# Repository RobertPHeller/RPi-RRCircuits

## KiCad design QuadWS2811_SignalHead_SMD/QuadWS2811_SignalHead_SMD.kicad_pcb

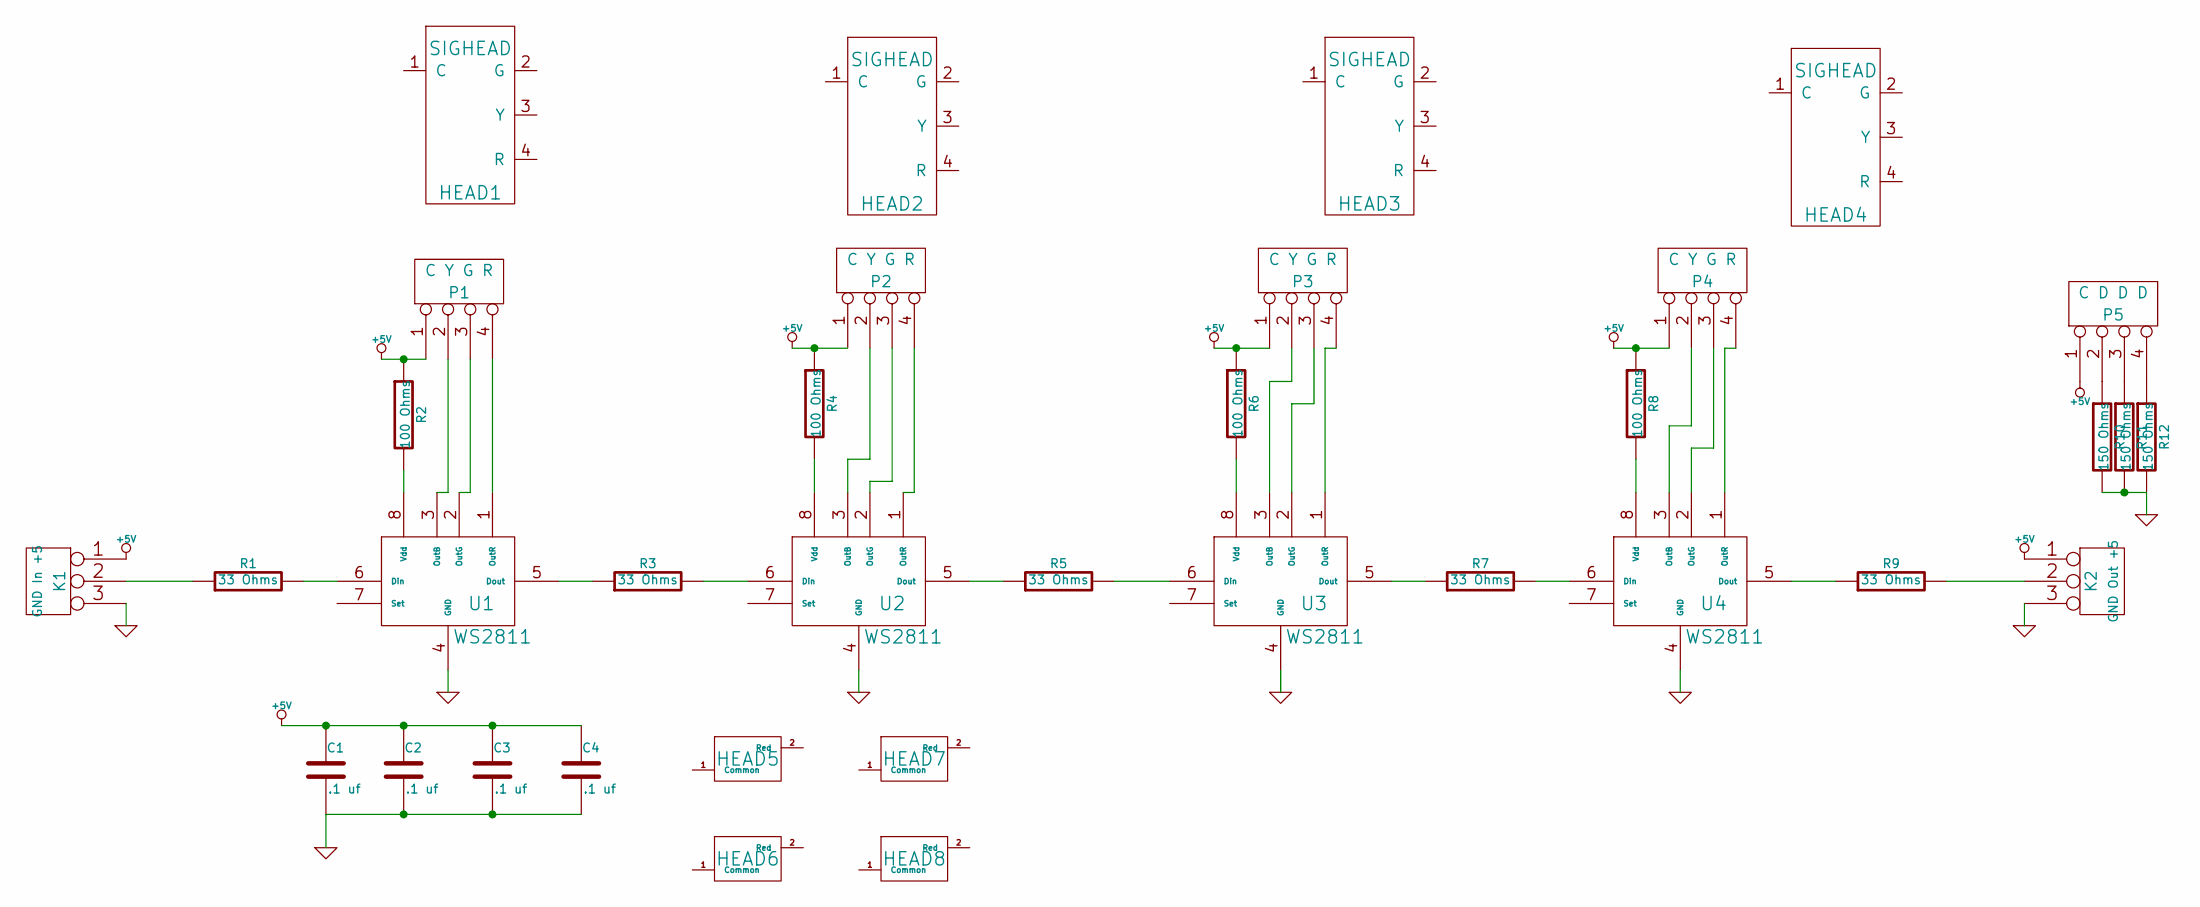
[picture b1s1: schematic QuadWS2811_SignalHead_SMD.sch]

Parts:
C1, C2, C3, C4: .1 uf
HEAD1, HEAD2, HEAD3, HEAD4: SIGHEAD
HEAD5, HEAD6, HEAD7, HEAD8: DUMMY
K1: GND In +5
K2: GND Out +5
P1, P2, P3, P4: C Y G R
P5: C D D D
R1, R3, R5, R7, R9: 33 Ohms
R2, R4, R6, R8: 100 Ohms
R10, R11, R12: 150 Ohms
U1, U2, U3, U4: WS2811

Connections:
+5V: C1.1, C2.1, C3.1, C4.1, K1.1, K2.1, P1.1, P2.1, P3.1, P4.1, P5.1, R2.1, R4.1, R6.1, R8.1
GND: C1.2, C2.2, C3.2, C4.2, K1.3, K2.3, R10.2, R11.2, R12.2, U1.4 (GND), U2.4 (GND), U3.4 (GND), U4.4 (GND)
unnamed: R2.2, U1.8 (Vdd)
unnamed: P1.2, U1.3 (OutB)
unnamed: P1.3, U1.2 (OutG)
unnamed: P1.4, U1.1 (OutR)
unnamed: R4.2, U2.8 (Vdd)
unnamed: P2.2, U2.3 (OutB)
unnamed: P4.4, U4.1 (OutR)
unnamed: P5.2, R10.1
unnamed: P5.3, R11.1
unnamed: P5.4, R12.1
unnamed: P2.3, U2.2 (OutG)
unnamed: P2.4, U2.1 (OutR)
unnamed: R6.2, U3.8 (Vdd)
unnamed: P3.2, U3.3 (OutB)
unnamed: P3.3, U3.2 (OutG)
unnamed: P3.4, U3.1 (OutR)
unnamed: P4.2, U4.3 (OutB)
unnamed: R8.2, U4.8 (Vdd)
unnamed: P4.3, U4.2 (OutG)
unnamed: R7.2, U4.6 (Din)
unnamed: R9.1, U4.5 (Dout)
unnamed: R3.1, U1.5 (Dout)
unnamed: R1.2, U1.6 (Din)
unnamed: R5.1, U2.5 (Dout)
unnamed: R3.2, U2.6 (Din)
unnamed: R7.1, U3.5 (Dout)
unnamed: R5.2, U3.6 (Din)
unnamed: K1.2 (PM), R1.1
unnamed: K2.2 (PM), R9.2

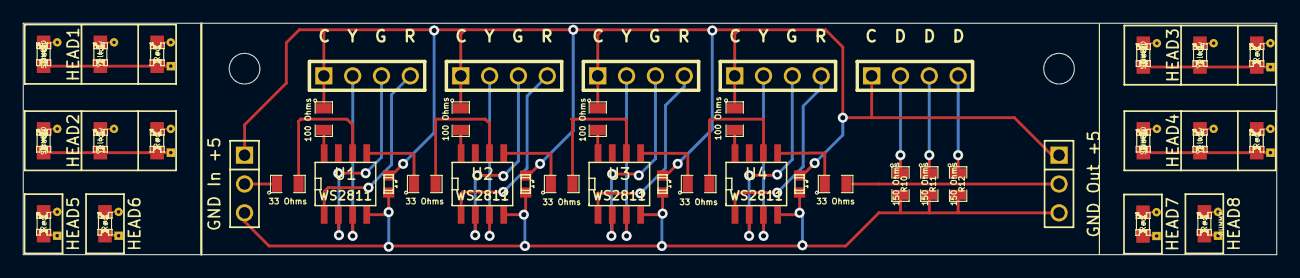
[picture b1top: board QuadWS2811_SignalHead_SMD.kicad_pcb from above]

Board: 2 copper layers, 110.4 x 20.4 mm, 37 parts (0 on the bottom side), 31 nets.

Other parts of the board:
MH: MountingHole_2-7mm_RevA_Date21Jun2010
MH#2: MountingHole_2-7mm_RevA_Date21Jun2010

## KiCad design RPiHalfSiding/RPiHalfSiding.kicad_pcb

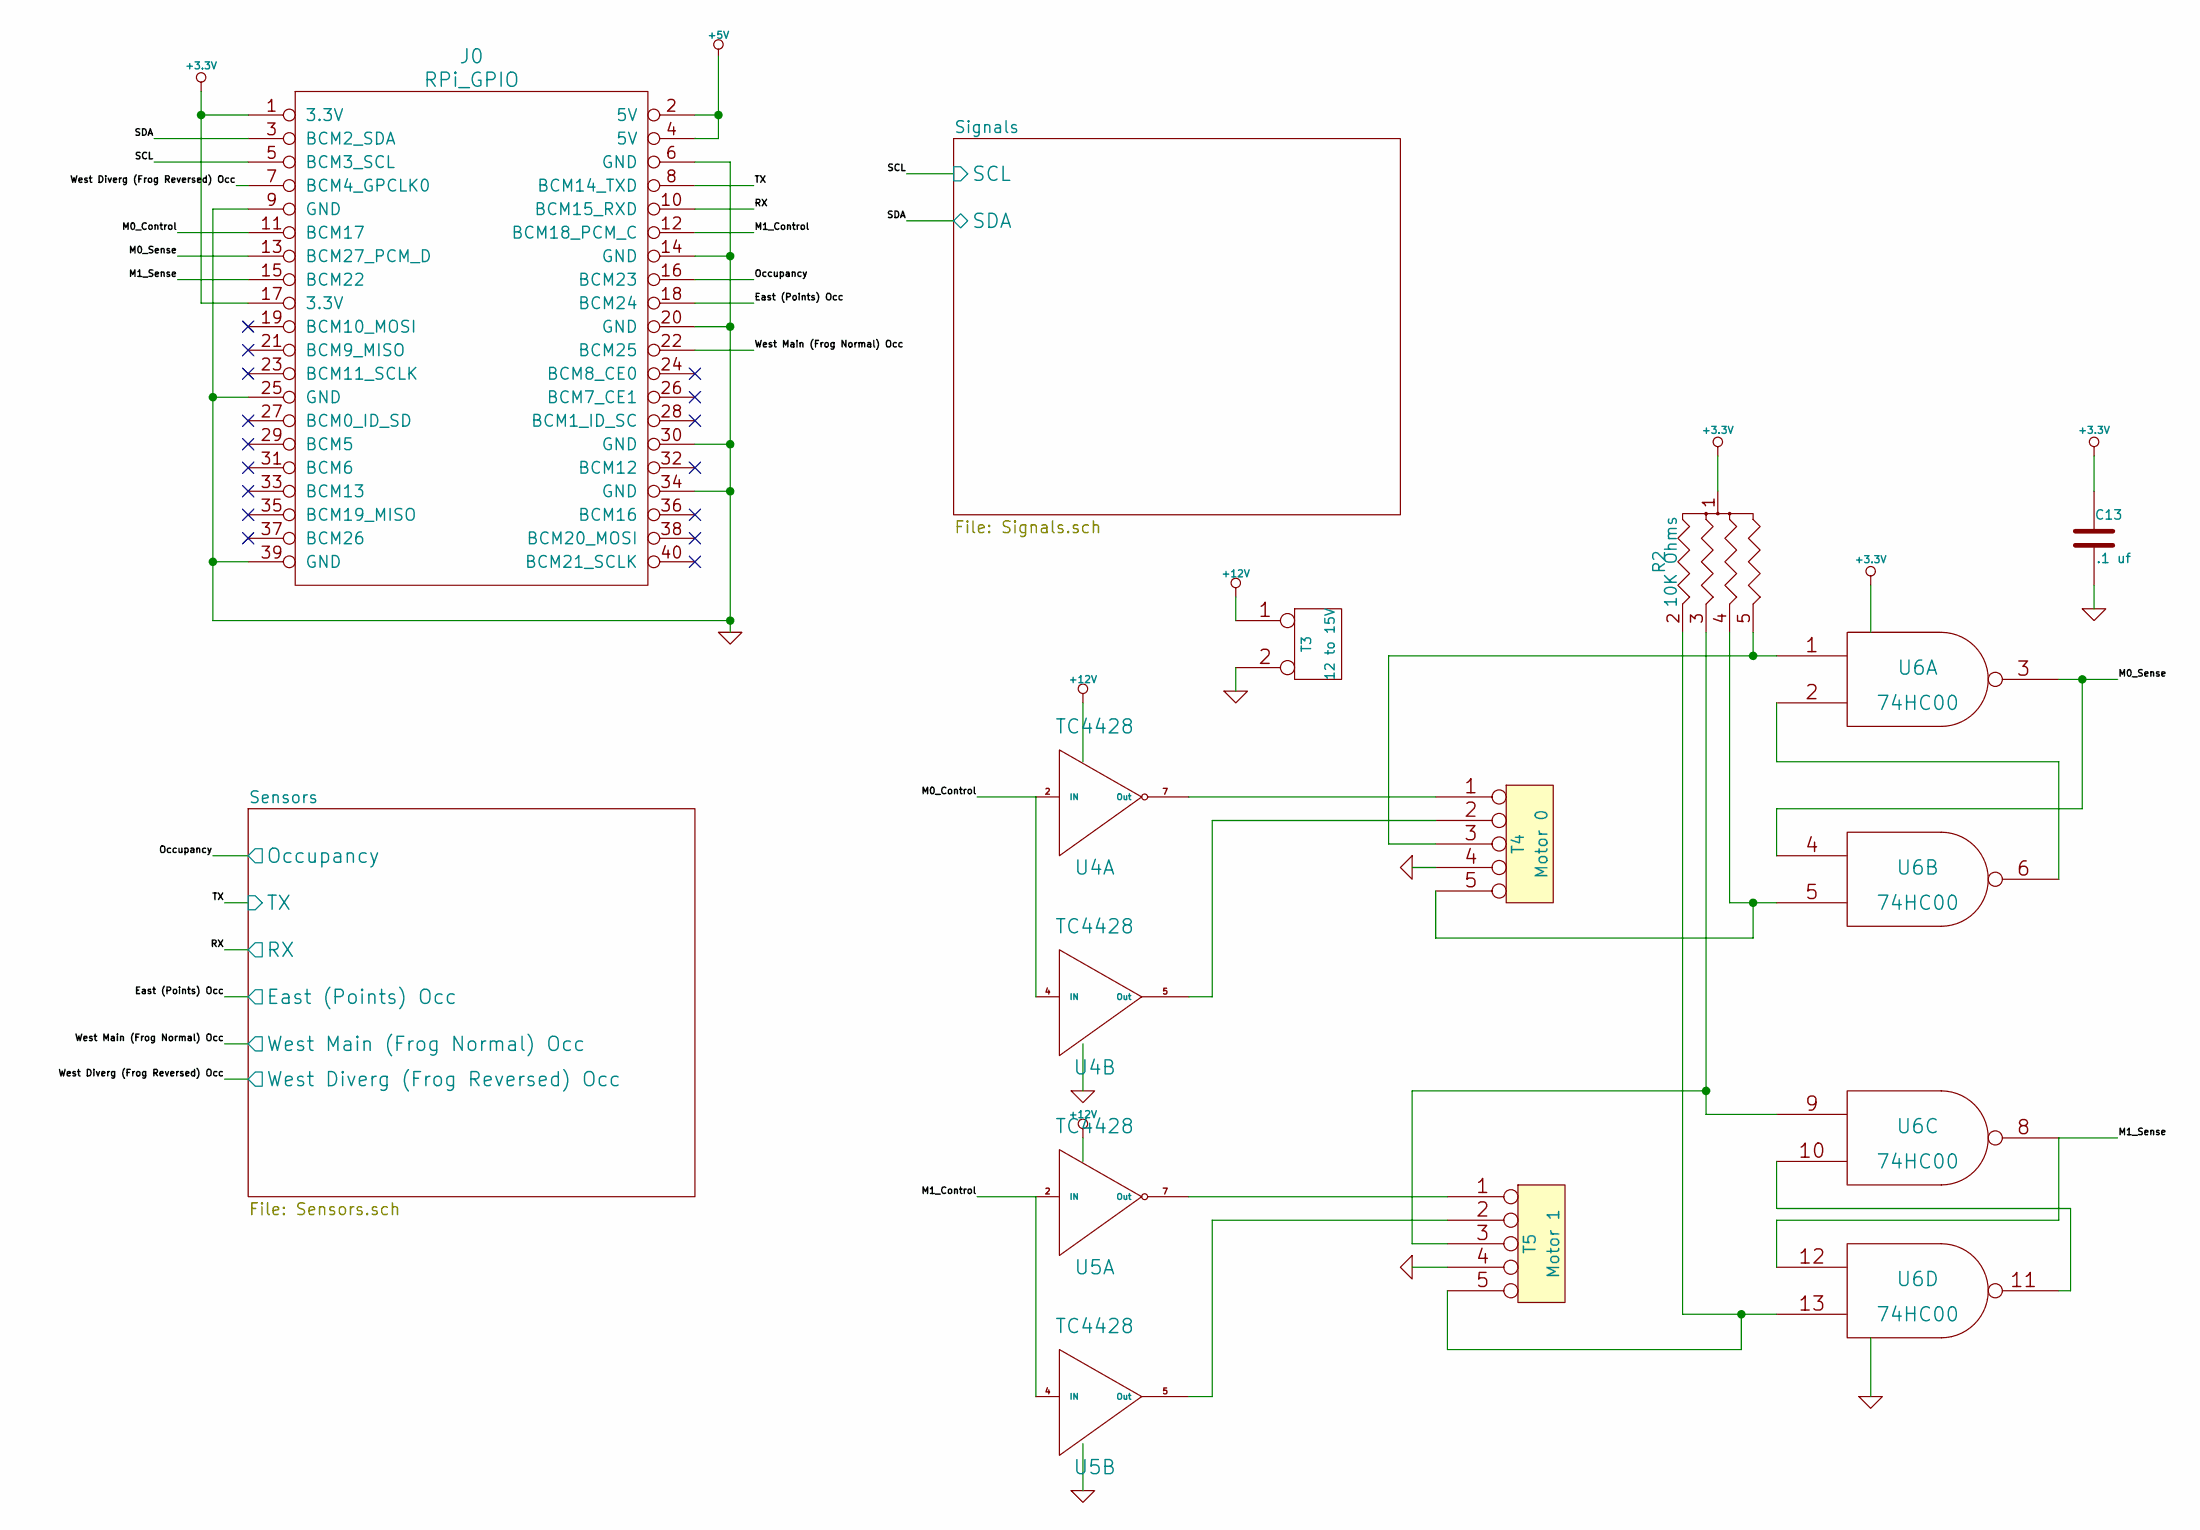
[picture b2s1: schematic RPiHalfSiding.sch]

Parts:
C13: .1 uf
J0: RPi_GPIO; Pin_Header_Straight_2x20
R2: 10K Ohms
T3: 12 to 15V
T4: Motor 0
T5: Motor 1
U4, U5: TC4428
U6: 74HC00

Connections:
+3.3V: C13.1, J0.1 (3.3V), J0.17 (3.3V), R2.1, U6.14 (VCC); also elsewhere on the board
+5V: J0.2 (5V), J0.4 (5V); also elsewhere on the board
+12V: T3.1, U4.6 (Vdd), U5.6 (Vdd)
/M0_Control: J0.11 (BCM17), U4.2 (IN), U4.4 (IN)
/M0_Sense: J0.13 (BCM27_PCM_D), U6.3, U6.4
/M1_Control: J0.12 (BCM18_PCM_C), U5.2 (IN), U5.4 (IN)
/M1_Sense: J0.15 (BCM22), U6.8, U6.12
/Sensors/East (Points) Occ: J0.18 (BCM24); also elsewhere on the board
/Sensors/Occupancy: J0.16 (BCM23); also elsewhere on the board
/Sensors/RX: J0.10 (BCM15_RXD); also elsewhere on the board
/Sensors/TX: J0.8 (BCM14_TXD); also elsewhere on the board
/Sensors/West Diverg (Frog Reversed) Occ: J0.7 (BCM4_GPCLK0); also elsewhere on the board
/Sensors/West Main (Frog Normal) Occ: J0.22 (BCM25); also elsewhere on the board
/Signals/SCL: J0.5 (BCM3_SCL); also elsewhere on the board
/Signals/SDA: J0.3 (BCM2_SDA); also elsewhere on the board
GND: C13.2, J0.6 (GND), J0.9 (GND), J0.14 (GND), J0.20 (GND), J0.25 (GND), J0.30 (GND), J0.34 (GND), J0.39 (GND), T3.2 (PM), T4.4, T5.4, U4.3 (GND), U5.3 (GND), U6.7 (GND); also elsewhere on the board
unnamed: U6.2, U6.6
unnamed: U6.10, U6.11
unnamed: T5.2, U5.5 (Out)
unnamed: R2.2, T5.5, U6.13
unnamed: R2.3, T5.3, U6.9
unnamed: R2.4, T4.5, U6.5
unnamed: R2.5, T4.3, U6.1
unnamed: T5.1, U5.7 (Out)
unnamed: T4.2, U4.5 (Out)
unnamed: T4.1, U4.7 (Out)

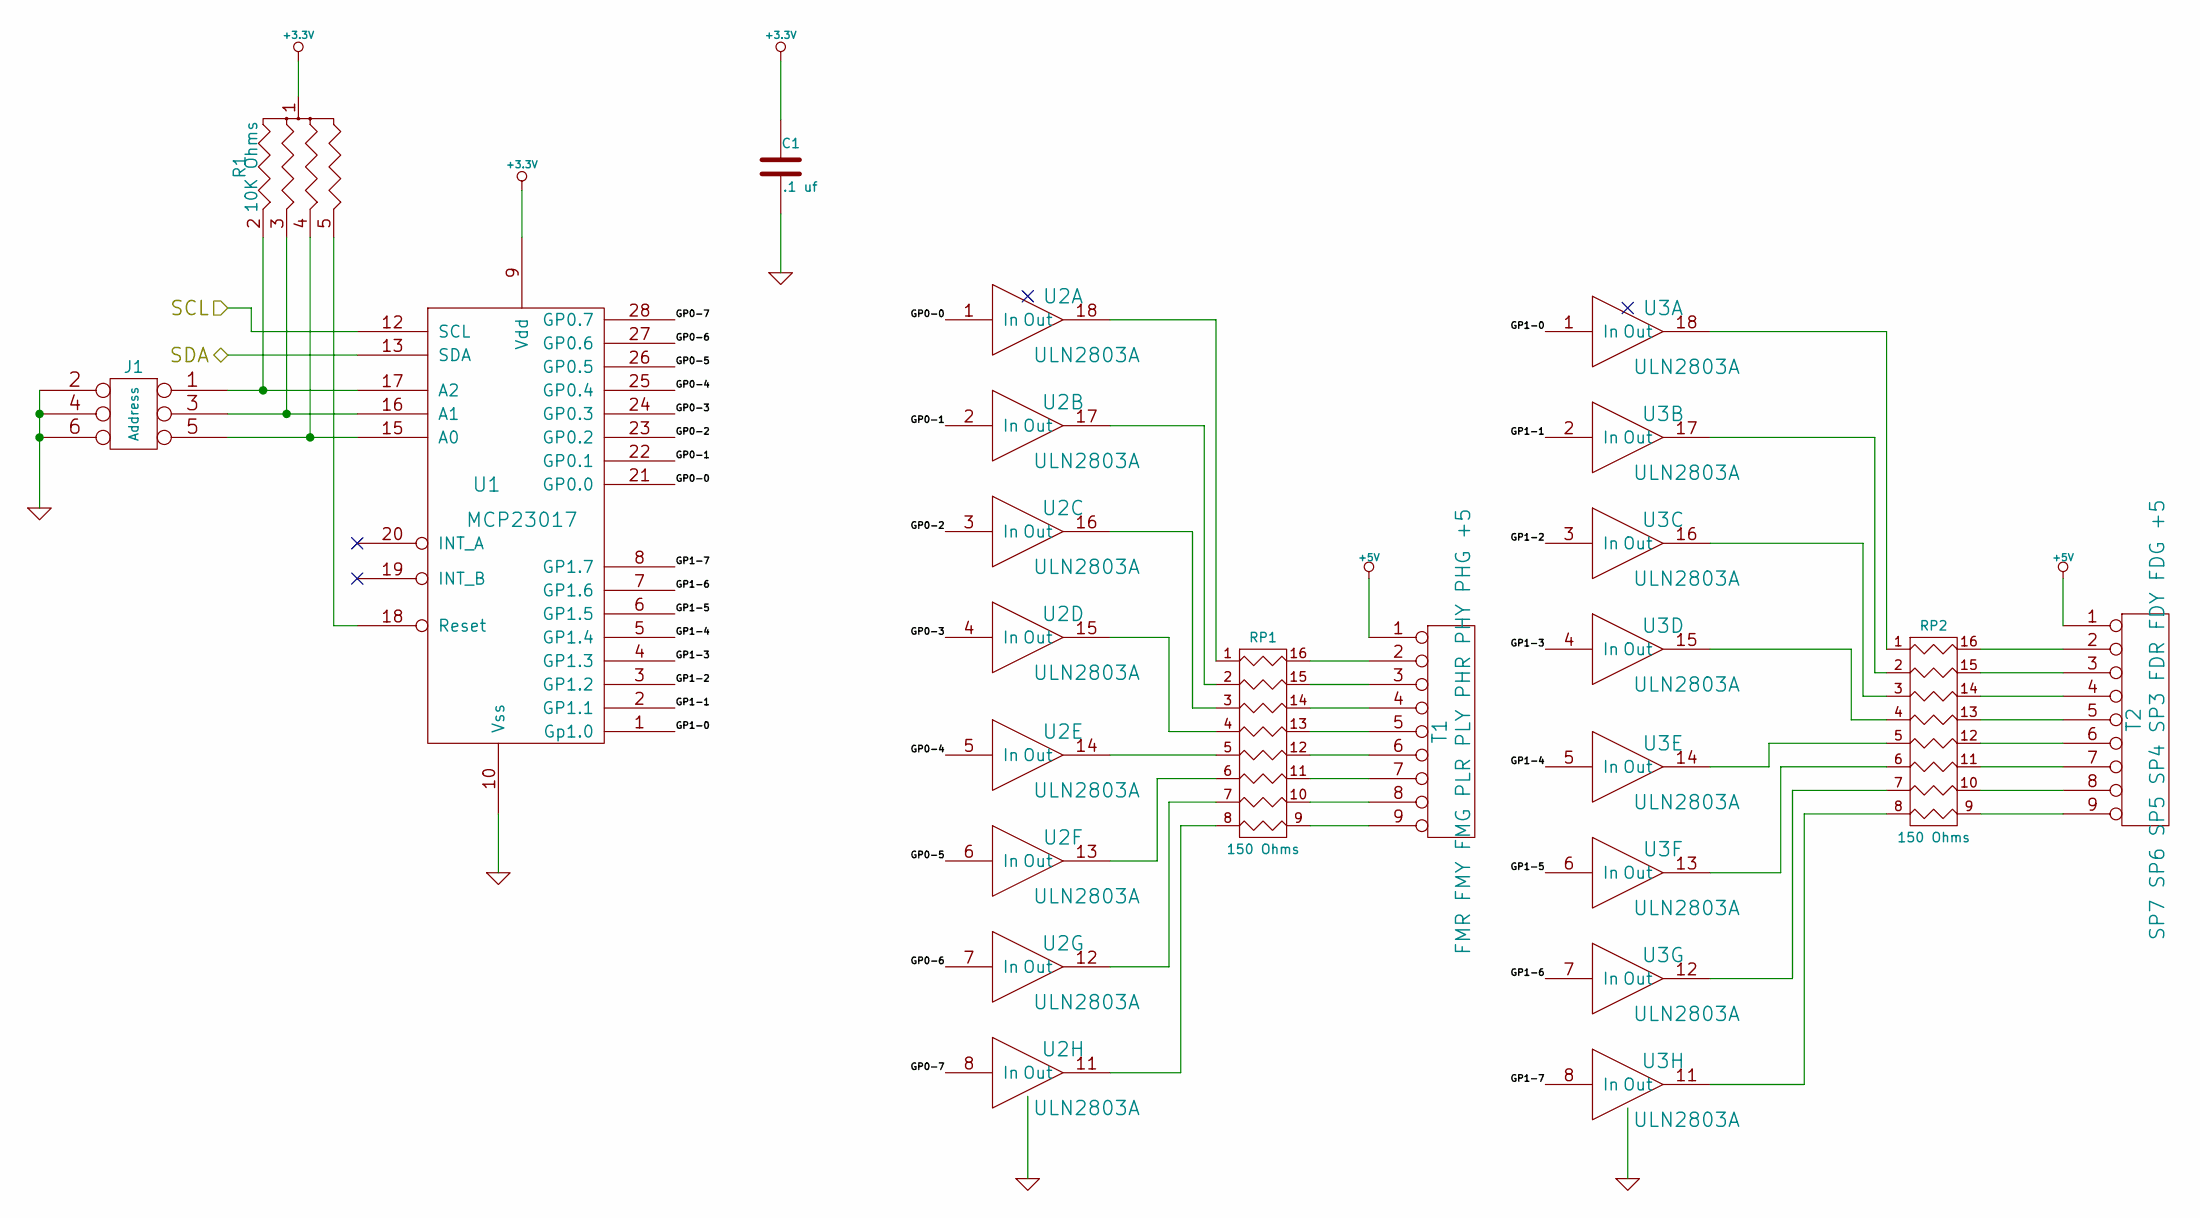
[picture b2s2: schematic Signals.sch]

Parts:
C1: .1 uf
J1: Address
R1: 10K Ohms
RP1, RP2: 150 Ohms
T1: FMR FMY FMG PLR PLY PHR PHY PHG +5
T2: SP7 SP6 SP5 SP4 SP3 FDR FDY FDG +5
U1: MCP23017
U2, U3: ULN2803A

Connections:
+3.3V: C1.1, R1.1, U1.9 (Vdd); also elsewhere on the board
+5V: T1.1, T2.1; also elsewhere on the board
/Signals/GP0-0: U1.21 (GP0.0), U2.1 (In)
/Signals/GP0-1: U1.22 (GP0.1), U2.2 (In)
/Signals/GP0-2: U1.23 (GP0.2), U2.3 (In)
/Signals/GP0-3: U1.24 (GP0.3), U2.4 (In)
/Signals/GP0-4: U1.25 (GP0.4), U2.5 (In)
/Signals/GP0-5: U1.26 (GP0.5), U2.6 (In)
/Signals/GP0-6: U1.27 (GP0.6), U2.7 (In)
/Signals/GP0-7: U1.28 (GP0.7), U2.8 (In)
/Signals/GP1-0: U1.1 (Gp1.0), U3.1 (In)
/Signals/GP1-1: U1.2 (GP1.1), U3.2 (In)
/Signals/GP1-2: U1.3 (GP1.2), U3.3 (In)
/Signals/GP1-3: U1.4 (GP1.3), U3.4 (In)
/Signals/GP1-4: U1.5 (GP1.4), U3.5 (In)
/Signals/GP1-5: U1.6 (GP1.5), U3.6 (In)
/Signals/GP1-6: U1.7 (GP1.6), U3.7 (In)
/Signals/GP1-7: U1.8 (GP1.7), U3.8 (In)
/Signals/SCL: U1.12 (SCL); also elsewhere on the board
/Signals/SDA: U1.13 (SDA); also elsewhere on the board
GND: C1.2, J1.2, J1.4, J1.6, U1.10 (Vss), U2.9 (GND), U3.9 (GND); also elsewhere on the board
unnamed: R1.5, U1.18 (Reset)
unnamed: J1.1, R1.2, U1.17 (A2)
unnamed: RP1.12 (R5), T1.6
unnamed: RP1.13 (R4), T1.5
unnamed: RP1.14 (R3), T1.4
unnamed: RP1.15 (R2), T1.3
unnamed: RP1.16 (R1), T1.2
unnamed: RP2.9 (R8), T2.9
unnamed: RP2.10 (R7), T2.8
unnamed: RP2.11 (R6), T2.7
unnamed: RP2.12 (R5), T2.6
unnamed: RP2.13 (R4), T2.5
unnamed: RP2.14 (R3), T2.4
unnamed: RP2.15 (R2), T2.3
unnamed: RP2.16 (R1), T2.2
unnamed: RP1.9 (R8), T1.9
unnamed: RP1.10 (R7), T1.8
unnamed: RP1.11 (R6), T1.7
unnamed: J1.5, R1.4, U1.15 (A0)
unnamed: J1.3, R1.3, U1.16 (A1)
unnamed: RP2.8, U3.11 (Out)
unnamed: RP2.7, U3.12 (Out)
unnamed: RP2.6, U3.13 (Out)
unnamed: RP1.7, U2.12 (Out)
unnamed: RP1.6, U2.13 (Out)
unnamed: RP1.5, U2.14 (Out)
unnamed: RP1.4, U2.15 (Out)
unnamed: RP1.3, U2.16 (Out)
unnamed: RP1.2, U2.17 (Out)
unnamed: RP1.1, U2.18 (Out)
unnamed: RP2.5, U3.14 (Out)
unnamed: RP2.4, U3.15 (Out)
unnamed: RP2.3, U3.16 (Out)
unnamed: RP2.2, U3.17 (Out)
unnamed: RP2.1, U3.18 (Out)
unnamed: RP1.8, U2.11 (Out)

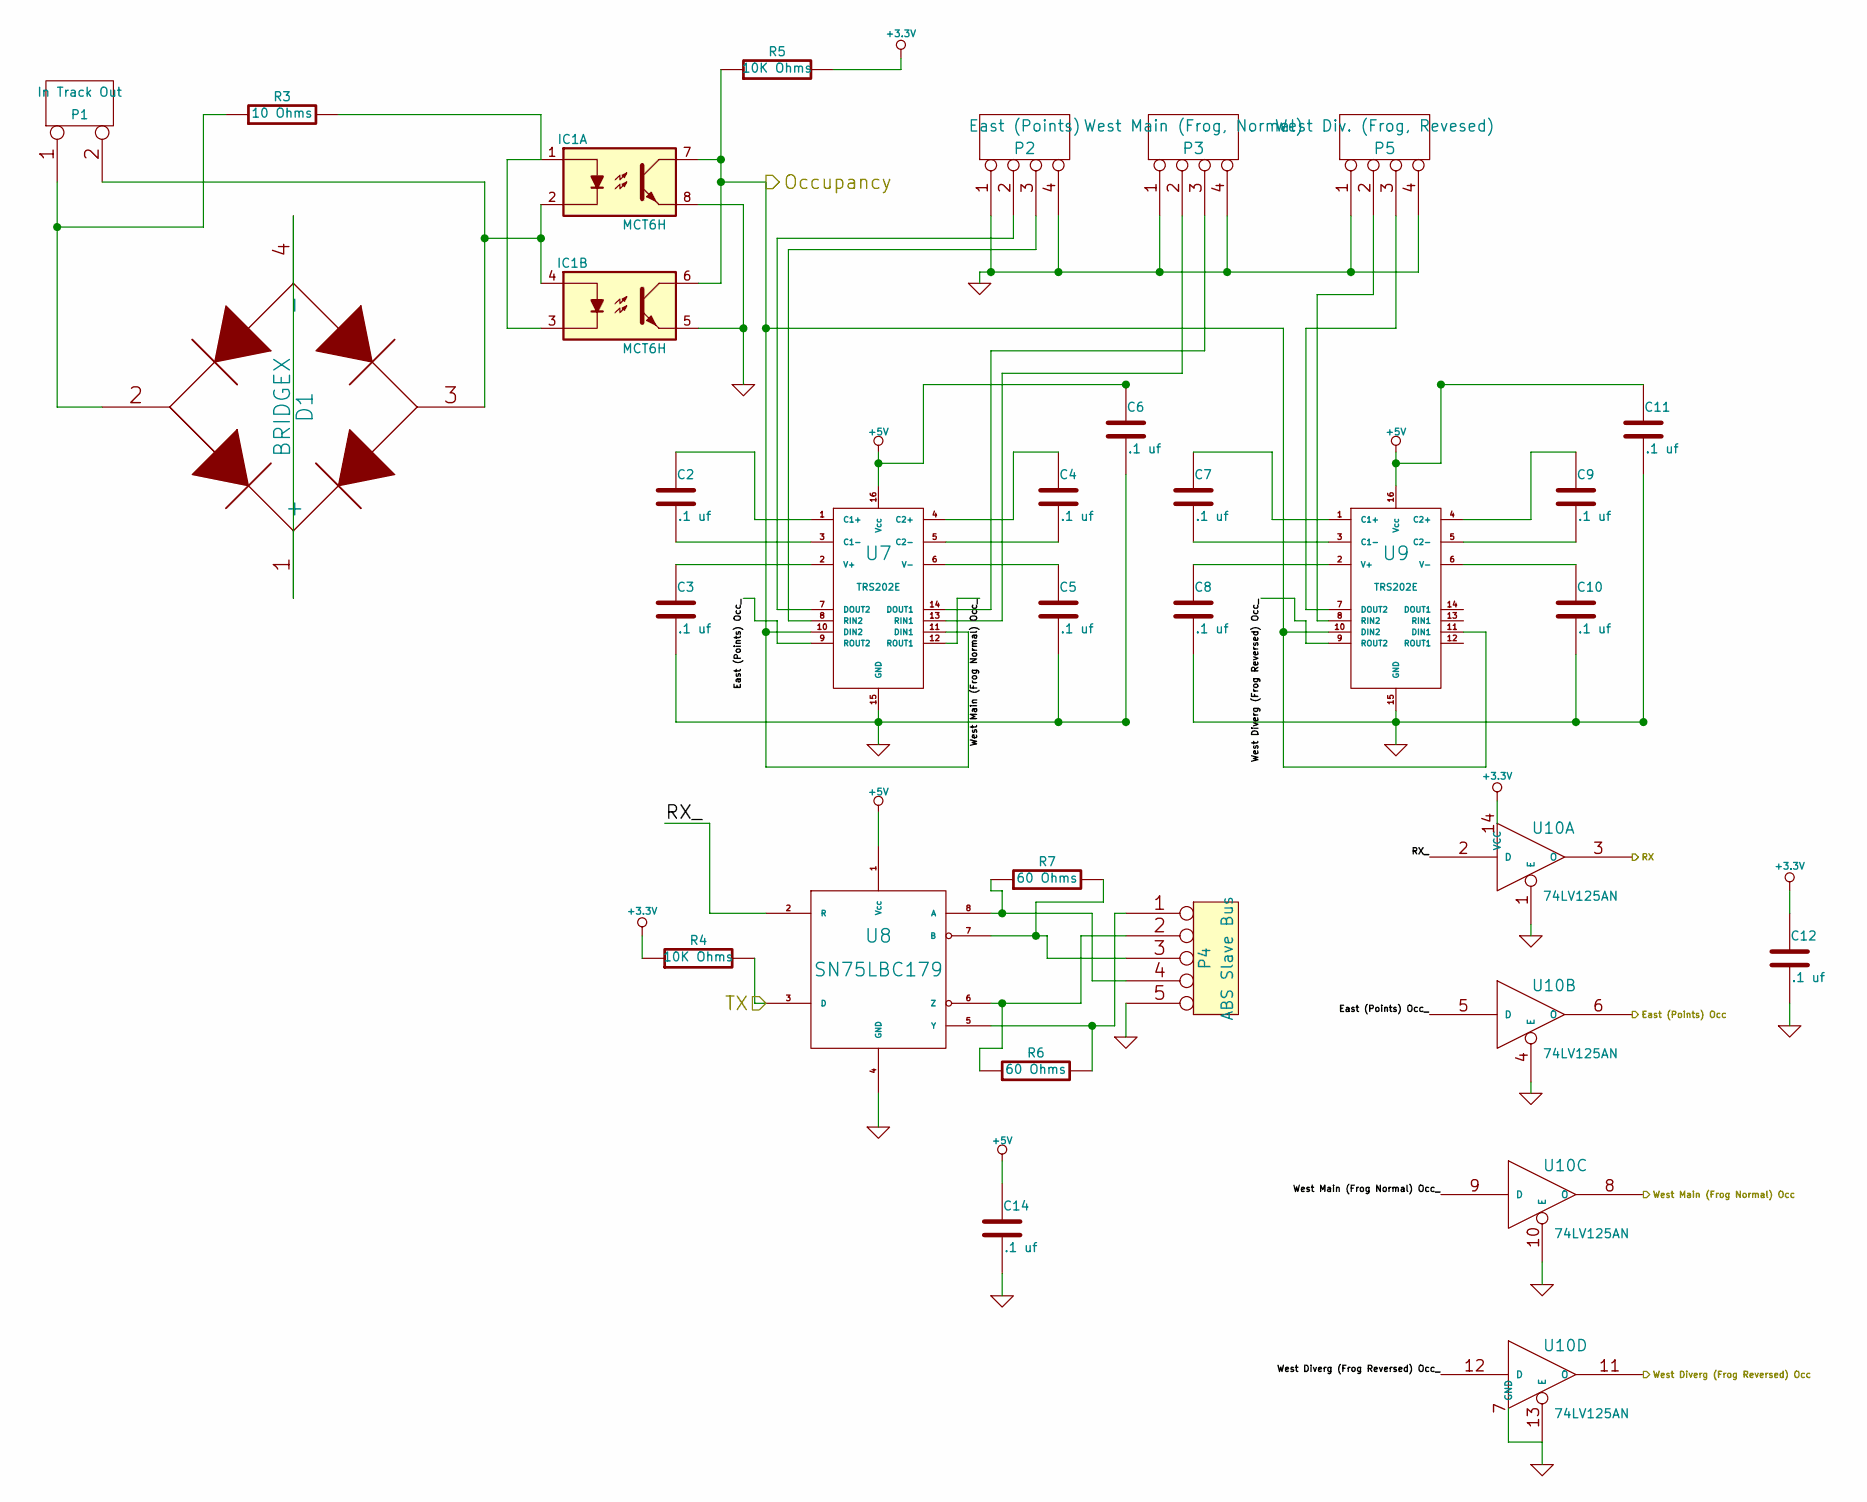
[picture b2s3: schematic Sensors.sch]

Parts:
C2, C3, C4, C5, C6, C7, C8, C9, C10, C11, C12, C14: .1 uf
D1: BRIDGEX
IC1: MCT6H; DIP-8__300
P1: In Track Out
P2: East (Points)
P3: West Main (Frog, Normal)
P4: ABS Slave Bus
P5: West Div. (Frog, Revesed)
R3: 10 Ohms
R4, R5: 10K Ohms
R6, R7: 60 Ohms
U7, U9: TRS202E
U8: SN75LBC179
U10: 74LV125AN

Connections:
+3.3V: C12.1, R4.1, R5.2, U10.14 (VCC); also elsewhere on the board
+5V: C6.1, C11.1, C14.1, U7.16 (Vcc), U8.1 (Vcc), U9.16 (Vcc); also elsewhere on the board
/Sensors/East (Points) Occ: U10.6 (O); also elsewhere on the board
/Sensors/East (Points) Occ_: U7.9 (ROUT2), U10.5 (D)
/Sensors/Occupancy: IC1.6, IC1.7, R5.1, U7.10 (DIN2), U7.11 (DIN1), U9.10 (DIN2), U9.11 (DIN1); also elsewhere on the board
/Sensors/RX: U10.3 (O); also elsewhere on the board
/Sensors/RX_: U8.2 (R), U10.2 (D)
/Sensors/TX: R4.2, U8.3 (D); also elsewhere on the board
/Sensors/West Diverg (Frog Reversed) Occ: U10.11 (O); also elsewhere on the board
/Sensors/West Diverg (Frog Reversed) Occ_: U9.9 (ROUT2), U10.12 (D)
/Sensors/West Main (Frog Normal) Occ: U10.8 (O); also elsewhere on the board
/Sensors/West Main (Frog Normal) Occ_: U7.12 (ROUT1), U10.9 (D)
GND: C3.2, C5.2, C6.2, C8.2, C10.2, C11.2, C12.2, C14.2, IC1.5, IC1.8, P2.1, P2.4, P3.1, P3.4, P4.5, P5.1, P5.4, U7.15 (GND), U8.4 (GND), U9.15 (GND), U10.1 (E), U10.4 (E), U10.7 (GND), U10.10 (E), U10.13 (E); also elsewhere on the board
unnamed: P2.2, U7.7 (DOUT2)
unnamed: P3.3, U7.14 (DOUT1)
unnamed: P5.2, U9.8 (RIN2)
unnamed: P3.2, U7.13 (RIN1)
unnamed: P2.3, U7.8 (RIN2)
unnamed: P5.3, U9.7 (DOUT2)
unnamed: C10.1, U9.6 (V-)
unnamed: C9.2, U9.5 (C2-)
unnamed: C8.1, U9.2 (V+)
unnamed: C7.2, U9.3 (C1-)
unnamed: C9.1, U9.4 (C2+)
unnamed: C7.1, U9.1 (C1+)
unnamed: D1.2, P1.1, R3.1
unnamed: D1.1 (+), D1.4 (-)
unnamed: IC1.1, IC1.3, R3.2
unnamed: D1.3, IC1.2, IC1.4, P1.2 (PM)
unnamed: P4.1, R6.2, U8.5 (Y)
unnamed: C5.1, U7.6 (V-)
unnamed: C4.1, U7.4 (C2+)
unnamed: C2.1, U7.1 (C1+)
unnamed: C4.2, U7.5 (C2-)
unnamed: C3.1, U7.2 (V+)
unnamed: C2.2, U7.3 (C1-)
unnamed: P4.3, R7.2, U8.7 (B)
unnamed: P4.4, R7.1, U8.8 (A)
unnamed: P4.2, R6.1, U8.6 (Z)

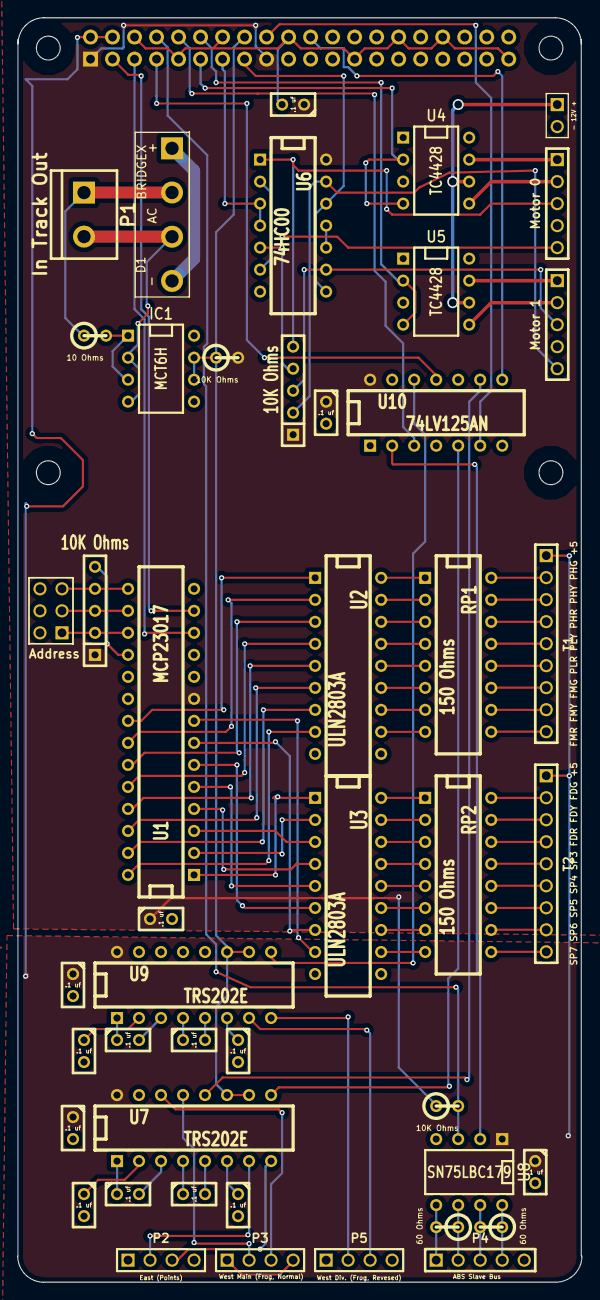
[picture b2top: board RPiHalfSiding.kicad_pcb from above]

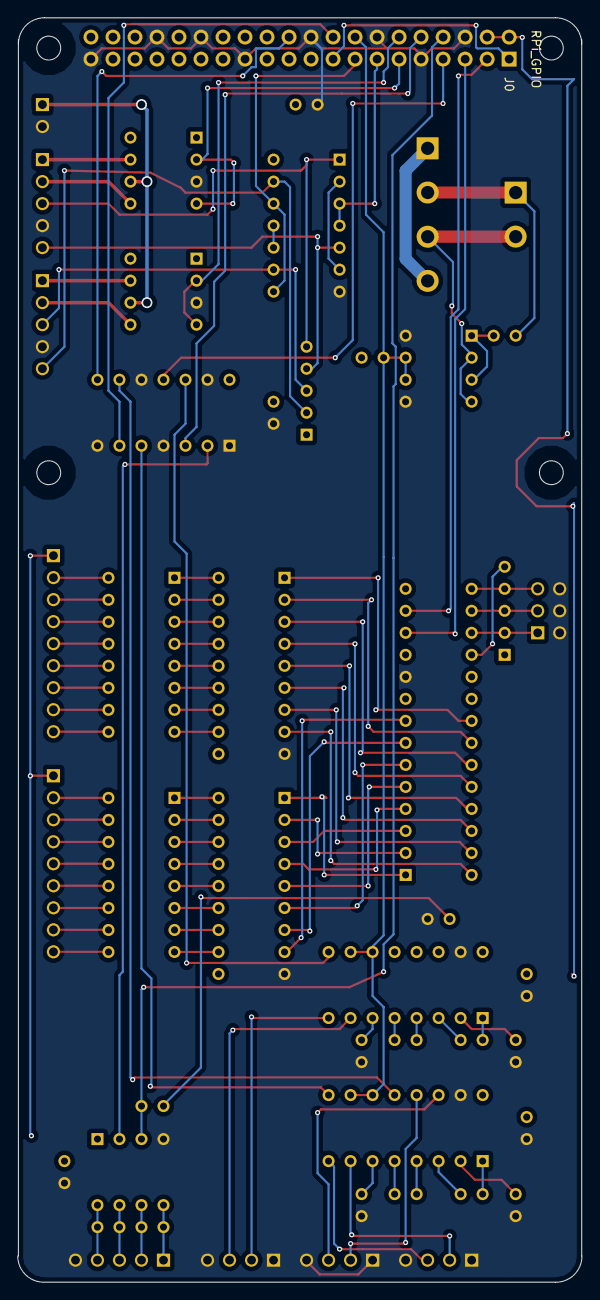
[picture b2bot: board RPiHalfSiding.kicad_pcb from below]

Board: 2 copper layers, 65.1 x 145.9 mm, 51 parts (5 on the bottom side), 108 nets.

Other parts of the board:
H1, H2, H3, H4: RPi_Hat_Mounting_Hole

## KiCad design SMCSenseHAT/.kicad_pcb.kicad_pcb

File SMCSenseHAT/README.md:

# SMCSenseHAT

This is a dual stall motor driver and point sense circuit.  The stall 
motor driver uses a MPQ3725A transistor to allow driving either multiple 
Tortoises in parallel (eg for a crossover) or newer Switchmaster or 
Torquemaster which draw more current than the LM324 can handle.  Also 
included is a point sense circuit built from a RS Flip Flop made from 
2-input NAND gates.  The point sense circuit expects to be connected to a 
single pole double throw switch, either a built in one in the Tortoise or 
an external one attached to the points themselves.  Uses GPIO 0, 1, 2, and 
3.

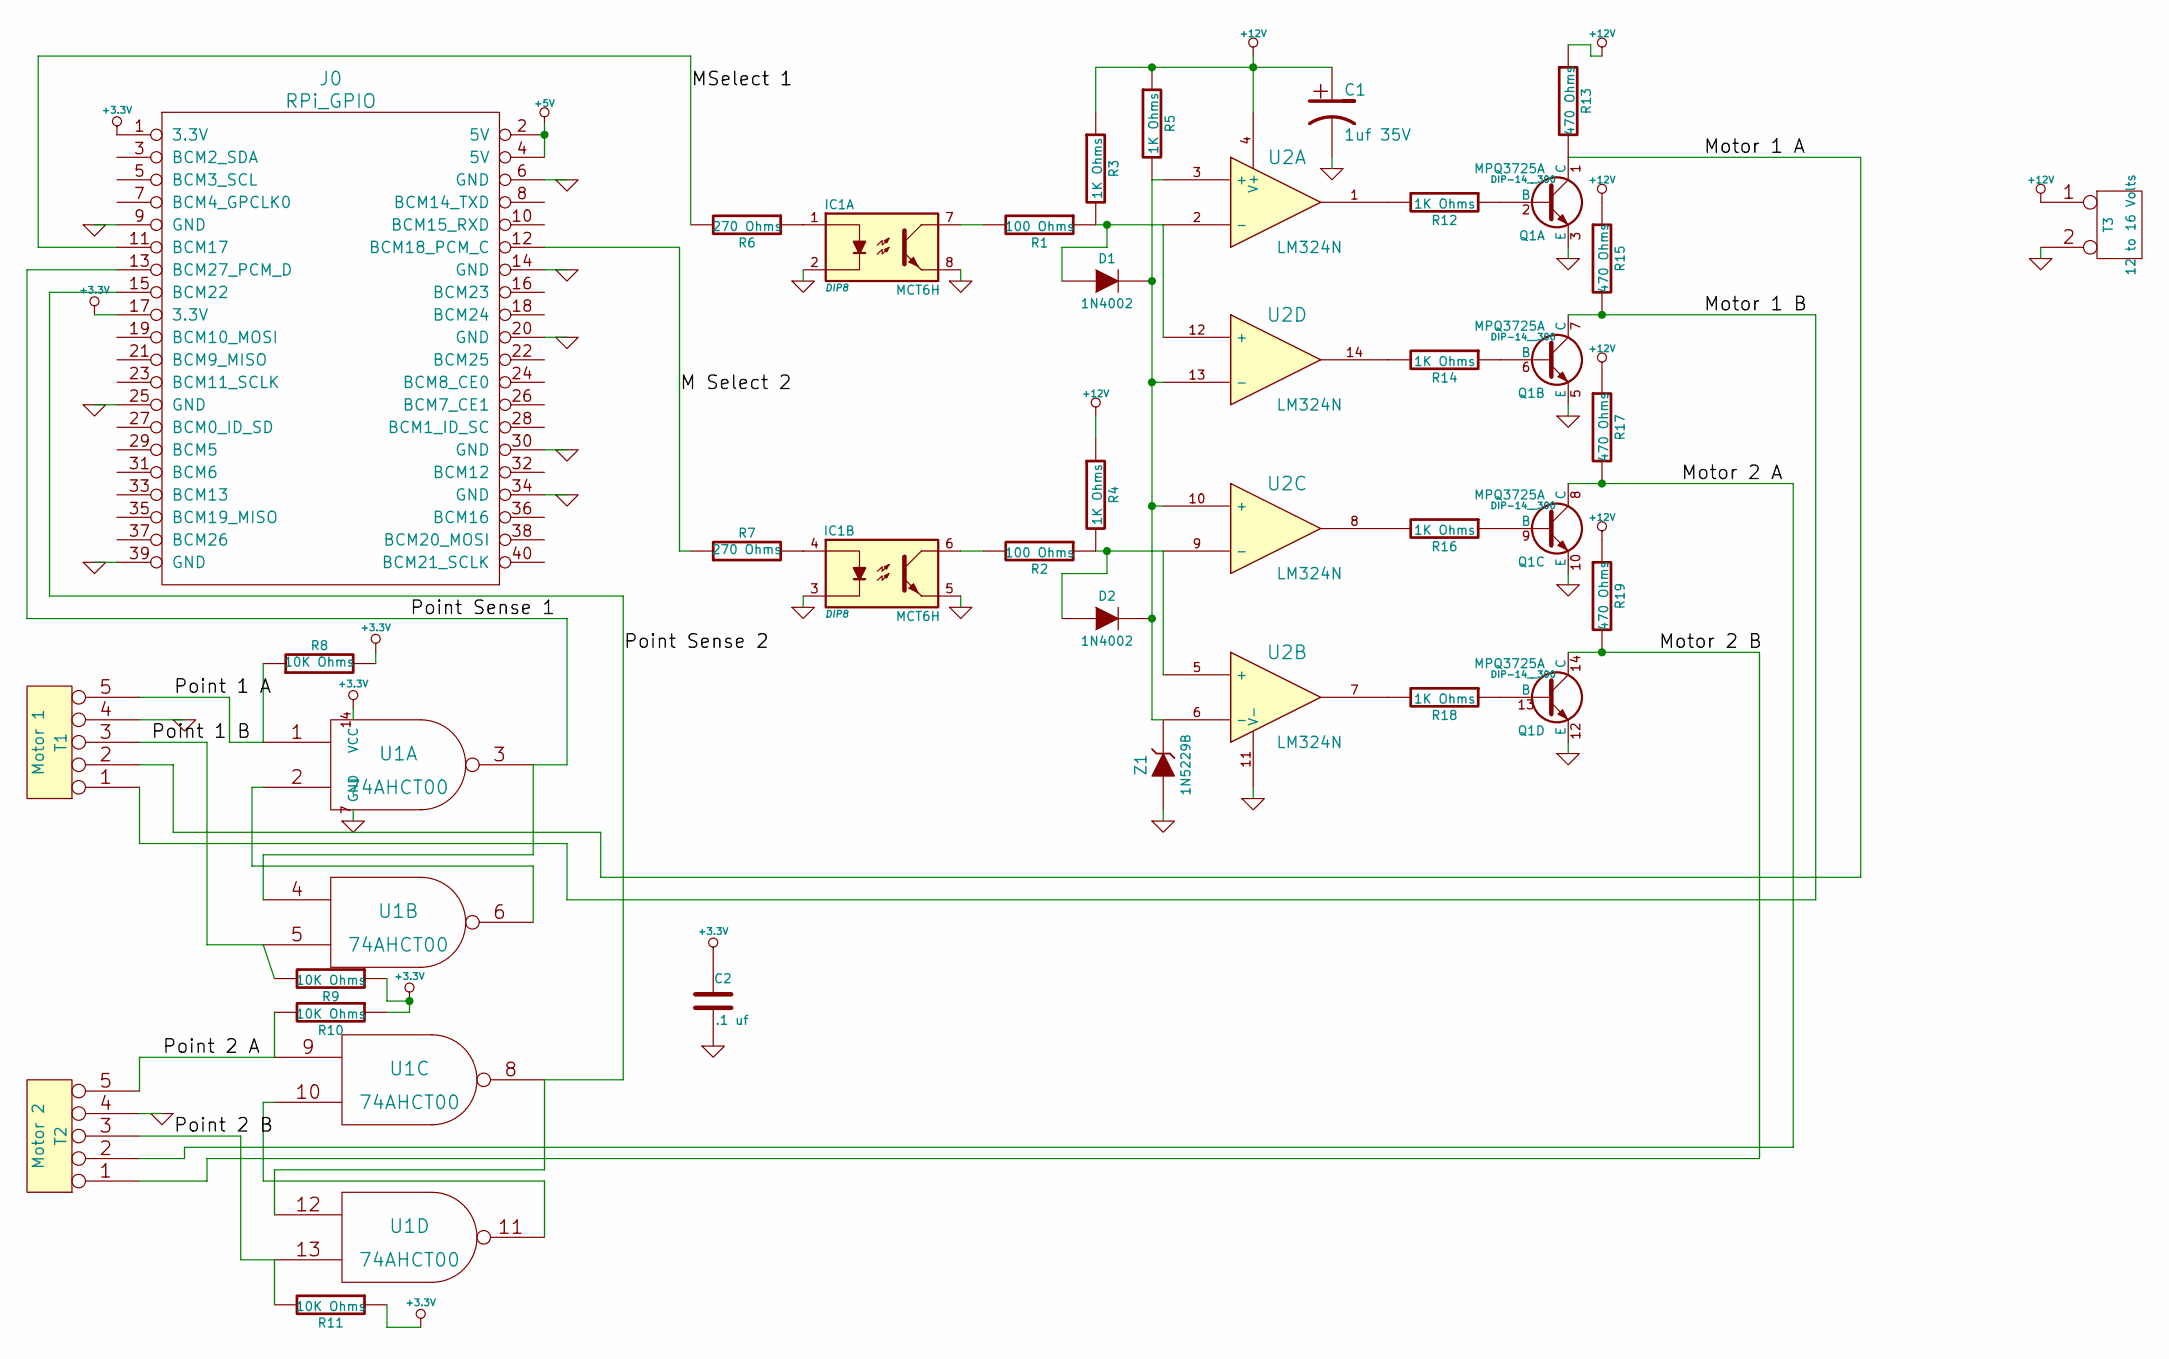
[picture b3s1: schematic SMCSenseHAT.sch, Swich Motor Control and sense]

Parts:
C1: 1uf 35V; Mouser Part Number 74-199D105X9035A1VE3
C2: .1 uf; Mouser part Number 21RZ310-RC
D1, D2: 1N4002; Mouser Part Number 833-1N4002-TP
IC1: MCT6H; DIP8; Mouser part Number 782-MCT6H
J0: RPi_GPIO; Pin_Header_Straight_2x20; Mouser Part Number 855-M20-6102045
Q1: MPQ3725A; DIP-14__300; Mouser part Number 610-MPQ3725A
R1, R2: 100 Ohms; Mouser Part Number 603-CFR-25JR-52100R
R3: 1K Ohms; Mouser part Number 279-2-1623927-3
R4, R5, R12, R14, R16, R18: 1K Ohms; Mouser Part Number 279-2-1623927-3
R6, R7: 270 Ohms; Mouser Part Number 603-CFR-25JR-52-270R
R8, R9, R10, R11: 10K Ohms; Mouser Part Number 603-CFR-25JR-5210K
R13: 470 Ohms; Mouser part Number 279-CFR50J470R
R15, R17: 470 Ohms; Mouser Part Number 279-CFR50J470R
R19: 470 Ohms; Mousere Part Number 279-CFR50J470R
T1: Motor 1; Mouser Part Number 571-282834-5
T2: Motor 2; Mouser Part Number 571-282834-5
T3: 12 to 16 Volts; Mouser Partnumber 571-282834-2
U1: 74AHCT00; Mouser part Number 595-SN74AHC00N
U2: LM324N; Mouser part Number 512-LM324N
Z1: 1N5229B; Mouser Part Number 512-1N5229BTR

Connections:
+3.3V: C2.1, J0.1 (3.3V), J0.17 (3.3V), R8.2, R9.1, R10.1, R11.1, U1.14 (VCC)
+5V: J0.2 (5V), J0.4 (5V)
+12V: C1.1, R3.1, R4.1, R5.1, R13.1, R15.1, R17.1, R19.1, T3.1, U2.4 (V+)
/M Select 2: J0.12 (BCM18_PCM_C), R7.1
/MSelect 1: J0.11 (BCM17), R6.2
/Motor 1 A: Q1.1 (C), R13.2, T1.2
/Motor 1 B: Q1.7 (C), R15.2, T1.1
/Motor 2 A: Q1.8 (C), R17.2, T2.2
/Motor 2 B: Q1.14 (C), R19.2, T2.1
/Point 1 A: R8.1, T1.5, U1.1
/Point 1 B: R9.2, T1.3, U1.5
/Point 2 A: R10.2, T2.5, U1.9
/Point 2 B: R11.2, T2.3, U1.13
/Point Sense 1: J0.13 (BCM27_PCM_D), U1.3, U1.4
/Point Sense 2: J0.15 (BCM22), U1.8, U1.12
GND: C1.2, C2.2, IC1.2, IC1.3, IC1.5, IC1.8, J0.6 (GND), J0.9 (GND), J0.14 (GND), J0.20 (GND), J0.25 (GND), J0.30 (GND), J0.34 (GND), J0.39 (GND), Q1.3 (E), Q1.5 (E), Q1.10 (E), Q1.12 (E), T1.4, T2.4, T3.2 (PM), U1.7 (GND), U2.11 (V-), Z1.1 (A)
unnamed: Q1.2 (B), R12.1
unnamed: R12.2, U2.1
unnamed: R14.2, U2.14
unnamed: Q1.6 (B), R14.1
unnamed: R16.2, U2.8
unnamed: Q1.9 (B), R16.1
unnamed: R18.2, U2.7
unnamed: Q1.13 (B), R18.1
unnamed: D1.1 (A), R1.1, R3.2, U2.2 (-), U2.12 (+)
unnamed: IC1.7, R1.2
unnamed: IC1.6, R2.2
unnamed: D2.1 (A), R2.1, R4.2, U2.5 (+), U2.9 (-)
unnamed: U1.2, U1.6
unnamed: D1.2 (K), D2.2 (K), R5.2, U2.3 (+), U2.6 (-), U2.10 (+), U2.13 (-), Z1.2 (K)
unnamed: IC1.4, R7.2
unnamed: IC1.1, R6.1
unnamed: U1.10, U1.11

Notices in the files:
SMCSenseHAT/.kicad_pcb.kicad_pcb:
Copyright 2016 Deepwoods Software
STM32F767ZI_LCC_Repeater/STM32F767ZI_LCC_Repeater.kicad_pcb:
(C) 2024 Robert Heller D/B/A Deepwoods Software
